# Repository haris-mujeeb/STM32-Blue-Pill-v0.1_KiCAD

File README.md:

# STM32-Blue-Pill-v0.1_KiCAD
Breakout Board for STM32F103C8T6 MCU

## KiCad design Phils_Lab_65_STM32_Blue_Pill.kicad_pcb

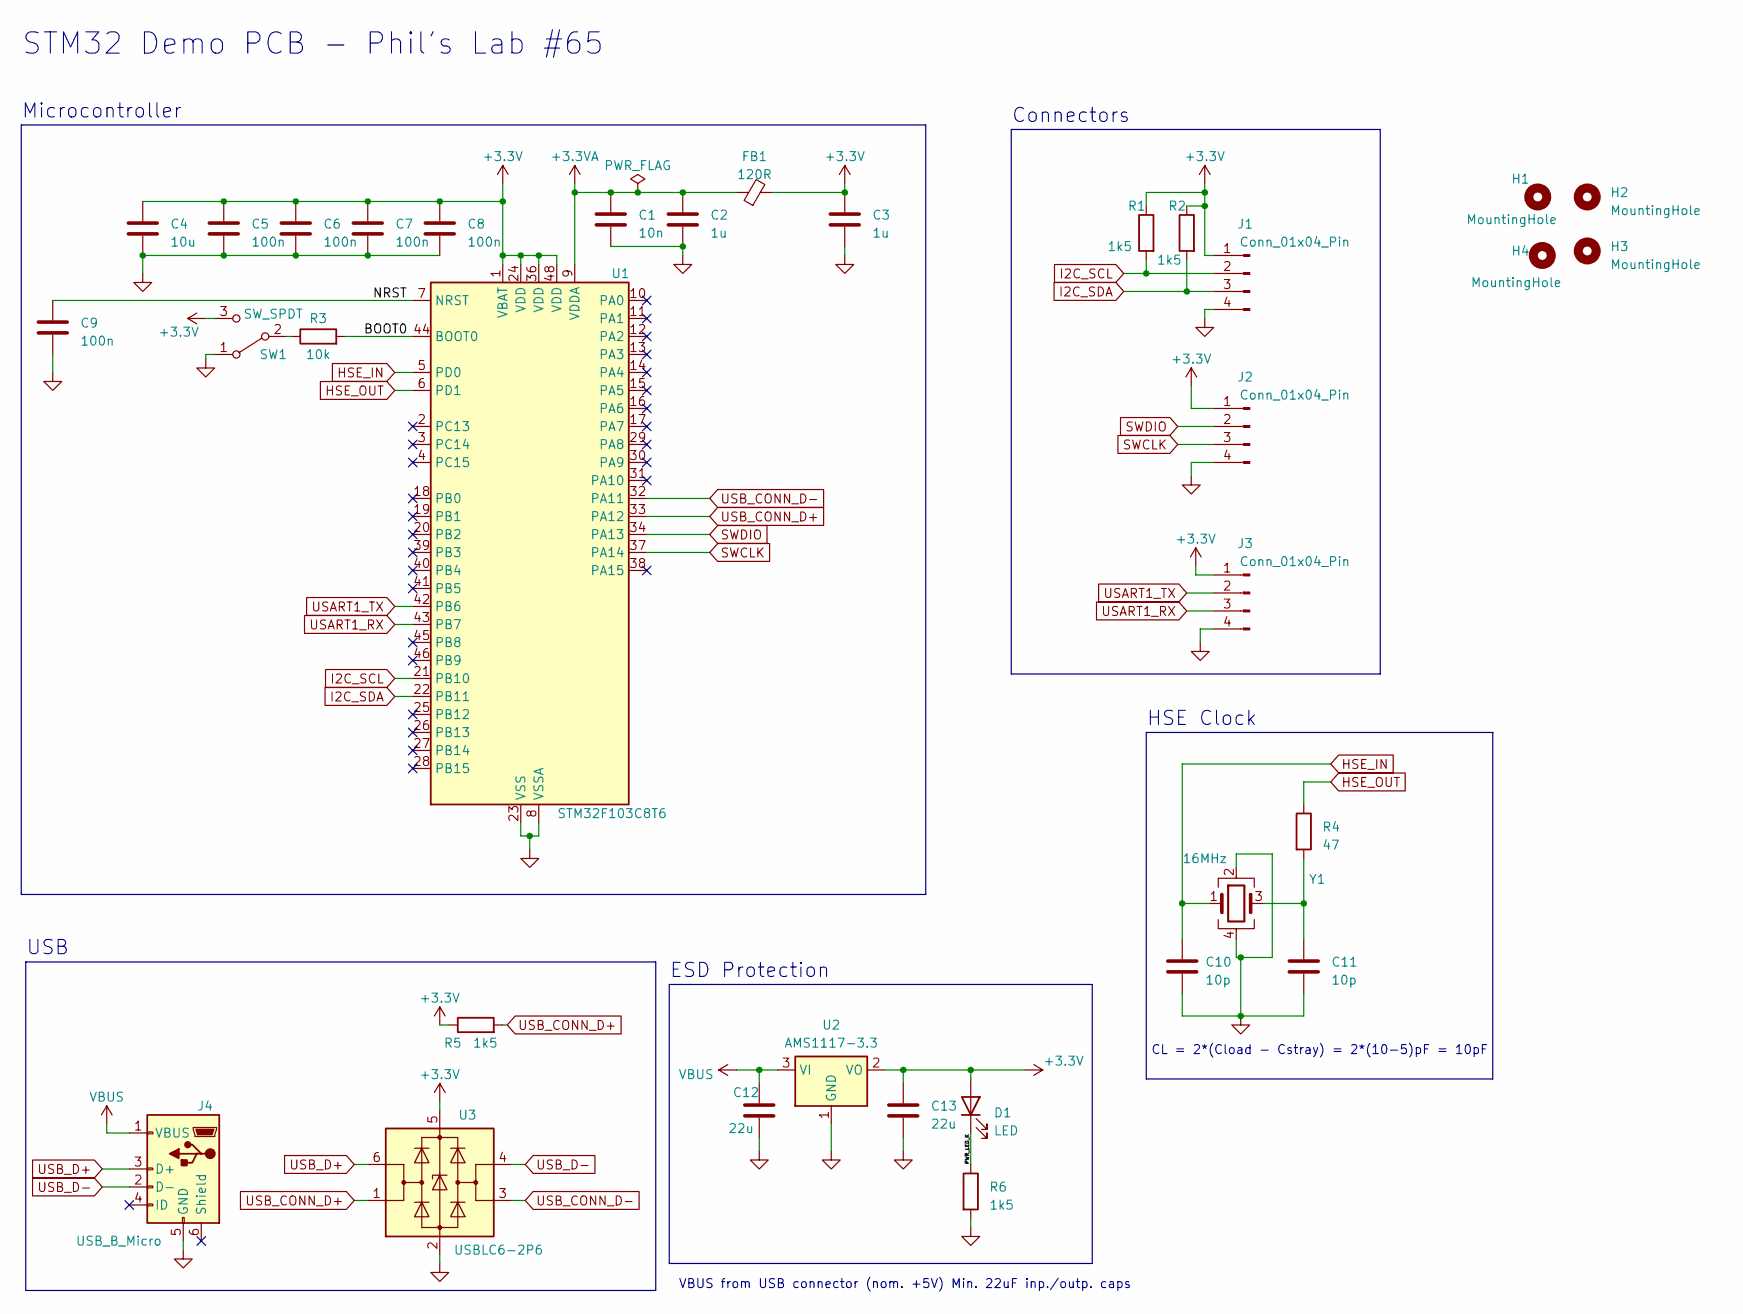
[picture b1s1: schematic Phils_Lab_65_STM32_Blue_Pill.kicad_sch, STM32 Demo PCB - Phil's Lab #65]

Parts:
C1: 10n; C_0402_1005Metric
C2, C3: 1u; C_0402_1005Metric
C4: 10u; C_0603_1608Metric
C5, C6, C7, C8, C9: 100n; C_0402_1005Metric
C10, C11: 10p; C_0402_1005Metric
C12, C13: 22u; C_0805_2012Metric
D1: LED; LED_0603_1608Metric
FB1: 120R; L_0603_1608Metric
H1, H2, H3, H4: MountingHole; MountingHole_2.2mm_M2
J1, J2, J3: Conn_01x04_Pin; PinHeader_1x04_P2.54mm_Vertical
J4: USB_B_Micro; USB_Micro-B_Wuerth_629105150521
R1, R2, R5, R6: 1k5; R_0402_1005Metric
R3: 10k; R_0402_1005Metric
R4: 47; R_0402_1005Metric
SW1: SW_SPDT; SW_SPDT_PCM12
U1: STM32F103C8T6; LQFP-48_7x7mm_P0.5mm
U2: AMS1117-3.3; SOT-223-3_TabPin2
U3: USBLC6-2P6; SOT-666
Y1: 16MHz; Crystal_SMD_3225-4Pin_3.2x2.5mm

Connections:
+3.3V: C3.1, C4.1, C5.1, C6.1, C7.1, C8.1, C13.1, D1.2 (A), FB1.2, J1.1, J2.1, J3.1, R1.1, R2.1, R5.1, SW1.3 (C), U1.1 (VBAT), U1.24 (VDD), U1.36 (VDD), U1.48 (VDD), U2.2 (VO), U3.5 (VBUS)
+3.3VA: C1.1, C2.1, FB1.1, U1.9 (VDDA)
/BOOT0: R3.2, U1.44 (BOOT0)
/NRST: C9.1, U1.7 (NRST)
/PWR_LED_K: D1.1 (K), R6.1
GND: C1.2, C2.2, C3.2, C4.2, C5.2, C6.2, C7.2, C8.2, C9.2, C10.2, C11.2, C12.2, C13.2, J1.4, J2.4, J3.4, J4.5 (GND), R6.2, SW1.1 (A), U1.8 (VSSA), U1.23 (VSS), U1.35 (VSS), U1.47 (VSS), U2.1 (GND), U3.2 (GND), Y1.2, Y1.4
HSE_IN: C10.1, U1.5 (PD0), Y1.1
HSE_OUT: R4.1, U1.6 (PD1)
I2C_SCL: J1.2, R1.2, U1.21 (PB10)
I2C_SDA: J1.3, R2.2, U1.22 (PB11)
unnamed: C11.1, R4.2, Y1.3
unnamed: R3.1, SW1.2 (B)
SWCLK: J2.3, U1.37 (PA14)
SWDIO: J2.2, U1.34 (PA13)
USART1_RX: J3.3, U1.43 (PB7)
USART1_TX: J3.2, U1.42 (PB6)
USB_CONN_D+: R5.2, U1.33 (PA12), U3.1 (I/O1)
USB_CONN_D-: U1.32 (PA11), U3.3 (I/O2)
USB_D+: J4.3 (D+), U3.6 (I/O1)
USB_D-: J4.2 (D-), U3.4 (I/O2)
VBUS: C12.1, J4.1 (VBUS), U2.3 (VI)

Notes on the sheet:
HSE Clock
USB
STM32 Demo PCB - Phil's Lab #65
Microcontroller
ESD Protection
Connectors
VBUS from USB connector (nom. +5V) Min. 22uF inp./outp. caps
CL = 2*(Cload - Cstray) = 2*(10-5)pF = 10pF

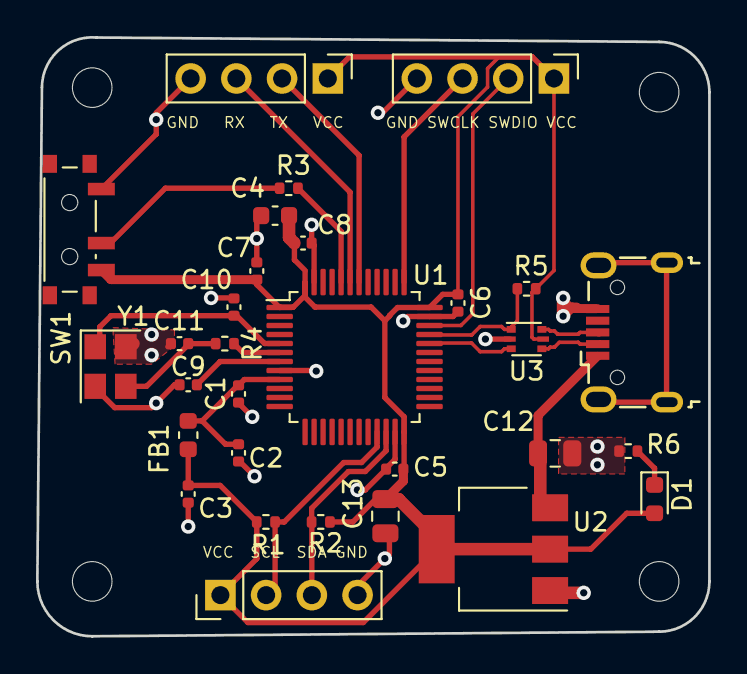
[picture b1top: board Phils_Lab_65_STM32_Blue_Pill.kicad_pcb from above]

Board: 2 copper layers, 37.3 x 33.3 mm, 34 parts (0 on the bottom side), 21 nets.

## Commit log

2023-11-14 v0.1
2023-11-14 photos
